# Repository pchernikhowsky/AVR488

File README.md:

# AVR488

A [Prologix](http://prologix.biz)<sup>TM</sup> compatible<sub><sup>(ish)</sup></sub> USB to [IEEE 488/GPIB/HP-IB](https://en.wikipedia.org/wiki/IEEE-488) controller interface based on the ATmega168/328 microcontroller.

## Description

I designed the AVR488 interface so that I could communicate with my various legacy Hewlett Packard / Agilent test instruments. There are numerous Arduino-based variations of USB/IEEE 488 interfaces out there already, but I prefer programming AVR devices down at the "bare metal" level using C code, so I came up with this version. Since it's necessary to construct a physical interface for the IEEE 488 connector anyway, it's easy enough to add an ATmega and driver ICs into that hardware design. Although it is intended to support a USB interface, a serial EIA-232 connection could also be implemented by deleting the USB interface IC and replacing it with an appropriate TTL to EIA-232 driver.

The embedded code size is approximately 13.5 KB and uses about 360 bytes of RAM, so there's more than enough free memory in an ATmega168 device. I have not included a bootloader (it avoids annoying startup delays and I prefer programming the ATmega directly using an ISP interface). If desired, there are many bootloaders available that could first be flashed to the device and then used to upload the AVR488 firmware.

**NOTE**: only controller mode (`++mode 1`) is implemented at this time, as I had no need for device mode. The latter is a possible future enhancement.

## Getting Started

### Dependencies

AVR488 supports both ATmega168 or ATmega328 devices (both the 10 and 20 MHz variants).

* Requires [MicroChip Studio 7 for AVR devices](https://www.microchip.com/en-us/tools-resources/develop/microchip-studio) for building the firmware.
* An ISP programmer (AVRISP MKII, AVR JTAG ICE, etc.) is needed to program the flash memory and set the fuses.

### Hardware Interfaces
* A USB 2.0 interface is provided by an [MCP2221A](https://www.microchip.com/en-us/product/MCP2221A) USB to TTL IC for connection to a host device (computer).
* The fully level-compliant IEEE 488 interface is implemented using the [SN75160](https://www.ti.com/lit/gpn/sn75als160) and [SN75161](https://www.ti.com/lit/gpn/sn75als161) driver ICs for connection to IEEE 488 devices.
* A direct serial EIA-232 interface could be implemented by using a [MAX232](https://www.ti.com/product/MAX232) (or equivalent) IC.

### Building and Installing the Firmware

1. Create a new project in MicroChip Studio and select the appropriate ATmega device.
2. Add the *.c and *.h files to the project.
3. Build the solution in MicroChip Studio.
4. Burn the code to your ATmega device.
5. Set the correct [fuses](Hardware/fuses.png):
   - Enable 8 MHz internal RC oscillator.
   - Disable divide by 8 clock divider (CKDIV8).
   - Enable brown-out detection (to provide protection against EEPROM corruption).
7. Connect the USB interface to a host computer and the IEEE 488 port to a device/instrument.
8. Upon first power-up, default settings will be stored in EEPROM. Settings can be changed and saved to EEPROM as required.
9. Enjoy!

When the AVR488 is first connected to a computer it will create a new USB serial port. The internal baud rate for the AVR488 serial port is fixed at 38400 bps (this can only be altered by changing a #define in the source code and reflashing). Thus, you MUST set the baud rate in your PC software (terminal program, etc.) to 38400 bps. A simple test to confirm that communications is fully working is to type the command "++help" (without the quotes). This should return a list available commands.

## Hardware Construction and Setup

You will need to construct your own hardware to support various ICs (ATmega168/328, MCP2221A, and SN75160/161) and the appropriate USB and IEEE 488 interface connectors. To make it easier, a full hardware design including [schematic](Hardware/AVR488-schematic.pdf), [bill of materials](Hardware/AVR488-BOM.csv), and PCB layout in KiCad format are provided. The PCB hardware and components have been selected to be hacker/hobbyist friendly; through-hole components are used exclusively. I ordered my PCBs from [JLCPCB](https://jlcpcb.com/), but feel free to use your preferred vendor. The PCB has been designed to fit inside a [Hammond 1593BB](https://www.hammfg.com/electronics/small-case/plastic/1593.pdf) plastic enclosure. A [dimensioned label](Hardware/AVR488-label.pdf) (including LED drilling dimensions) is also provided.

For simplicity, and to save pins, the internal 8 MHz RC oscillator in the ATmega168/328 is used as the clock source, so no external oscillator or crystal is required.

For diagnostic purposes, three LED outputs are provided:
* TE (Talk Enable): flashes when the TE signal to the IEEE 488 drivers goes high for driving data onto the bus.
* SRQ (Service Request): lights when the SRQ line is asserted, indicating that a device requires polling for status.
* STATUS: flashes during startup and then is continuously toggled when the watchdog timer is reset to indicate active processing (the toggling is around 130 kHz, so the LED is slightly dimmer than when fully on).

## Command List

The AVR488 command set is intended to be mostly compatible with the [Prologix GPIB-USB (HPIB-USB Controller)](http://prologix.biz/gpib-usb-controller.html). All commands are preceded by two plus signs (++). Any input not preceded by ++ is passed directly to the connected device(s). Input and commands from the host are buffered in a 254 byte buffer and then transmitted when either a CR (carriage return) or LF (line feed) character is received from the host. Not all Prologix commands have been implemented, and some do not operate exactly the same as the Prologix interface. Also, some extensions have been added for troubleshooting purposes (e.g., `debug` and `xdiag`) or for ease of use (e.g., `echo`).

Values enclosed in `[]` are optional. If a value is provided, the `[]` should not be included.

#### `++addr [n]`
Tell the interface which device to address (must be between 1 and 30). If no address is specified, the current device address will be displayed.

#### `++auto [n]`
Enable (1) or disable (0) automatic read-after-write when a "?" is included in the command sent to the device. If no value is provided, the current auto setting will be displayed.

#### `++clr`
Send a Select Device Clear (SDC) command to the currently addressed device.

#### `++debug [n]`
Enable simple (1), more verbose (2), or disable (0) debug logging messages. Convenient for troubleshooting problematic connections. If no value is provided, the current debug setting will be displayed.

#### `++default`
Emulates functionality of the AR488 command with the same name. The interface configuration is set with the following parameters:
* auto:	0
* eoi:	0 (disabled)
* eos:	0 (CR+LF)
* eot_enable:	0 (disabled)
* eot_char:	0
* address: 0
* read_tmo_ms:	1200
* echo: 0
* debug: 0

#### `++echo [n]`
Enable (1) or disable (0) echoing of characters received from USB port. Most IEEE 488 adapters require the sending application to enable local echo, but this is provided as an alternative. If no value is provided, the current echo setting will be displayed.

#### `++eoi [n]`
Enable (1) or disable (0) asserting the EOI line when the last byte is sent. If no value is provided, the current eoi setting will be displayed.

#### `++eos [n]`
Select the terminator characters to be appended to messages sent to the device: 0=CR+LF, 1=CR, 2=LF, 3=None. If no value is provided, the current eos setting will be displayed.

#### `++eot_char [n]`
ASCII code of character to be appended to messages received from the device (when EOI is used). If no value is provided, the current eot_char setting will be displayed.

#### `++eot_enable [n]`
Controls whether the eot_char is apprended to received messages. If no value is provided, the current eot_enable setting will be displayed.

#### `++help`
Print a list of commands and explanations.

#### `++ifc`
Issue an IEEE 488 interface clear by asserting the IFC line for 150 microseconds.

#### `++llo`
Disable front panel operation of the currently addressed device by sending the Local Lockout (LLO) command.

#### `++loc`
Enable front panel operation of the currently addressed device by sending the Go To Local (GTL) command.

#### `++mode [n]`
Compatibility-only command - we are always a controller. Any value provided is ignored and queries always return mode 1.

#### `++read`
Read from the currently addressed device until the eos terminating characters are received or a timeout occurs.

#### `++read eoi`
Read from the currently addressed device until either EOI is asserted, the eos terminating characters are received, or a timeout occurs.

#### `++read_tmo_ms [n]`
Sets the timeout value, in milliseconds, for the read and spoll commands. The default timeout is 1000 ms. If no value is provided, the current read_tmo_ms setting will be displayed.

#### `++rst`
Performs a power-on reset of the controller interface by forcing a watchdog timer timeout. Takes approximately 2 seconds.

#### `++savecfg 1`
Saves the current settings to EEPROM. Settings saved include: addr, eot_char, eot_enable, eos, eoi, auto, debug, and echo. Settings are **not** saved automatically when they are changed (to prevent unnecessary wear on the EEPROM). The value "1" must be included or the command is ignored.

#### `++spoll [n]`
Read the device status byte by issuing a Serial Poll command. If no address is specified the serial poll request will be sent to the currently addressed device.

#### `++srq`
Query the status of SRQ line. Returns 0 if the line is not asserted and 1 if asserted.

#### `++trg [n]`
Issue a Group Execute Trigger (GET) to a device. If no address is specified the trigger will be sent to the currently addressed device.

#### `++ver`
Query the current AVR488 firmware version.

#### `++xdiag`
Show the current state of the ATmega IO pins (for troubleshooting purposes).

## Version History

* 1.1
    * Firmware changes to improve AR488 and Prologix compatibility.
* 1.0
    * Initial Release

## License

This project is licensed under the GPL-3.0 License. See the [LICENSE](LICENSE) file for details.

## Acknowledgments

Inspiration, code snippets, libraries.
* [AR488](https://github.com/Twilight-Logic/AR488)
* [atmega-gpib](https://github.com/pepaslabs/atmega-gpib)
* [gpibusb-firmware](https://github.com/Galvant/gpibusb-firmware)
* [Peter Fleury's interrupt-driven UART library](http://www.peterfleury.epizy.com/doxygen/avr-gcc-libraries/group__pfleury__uart.html)

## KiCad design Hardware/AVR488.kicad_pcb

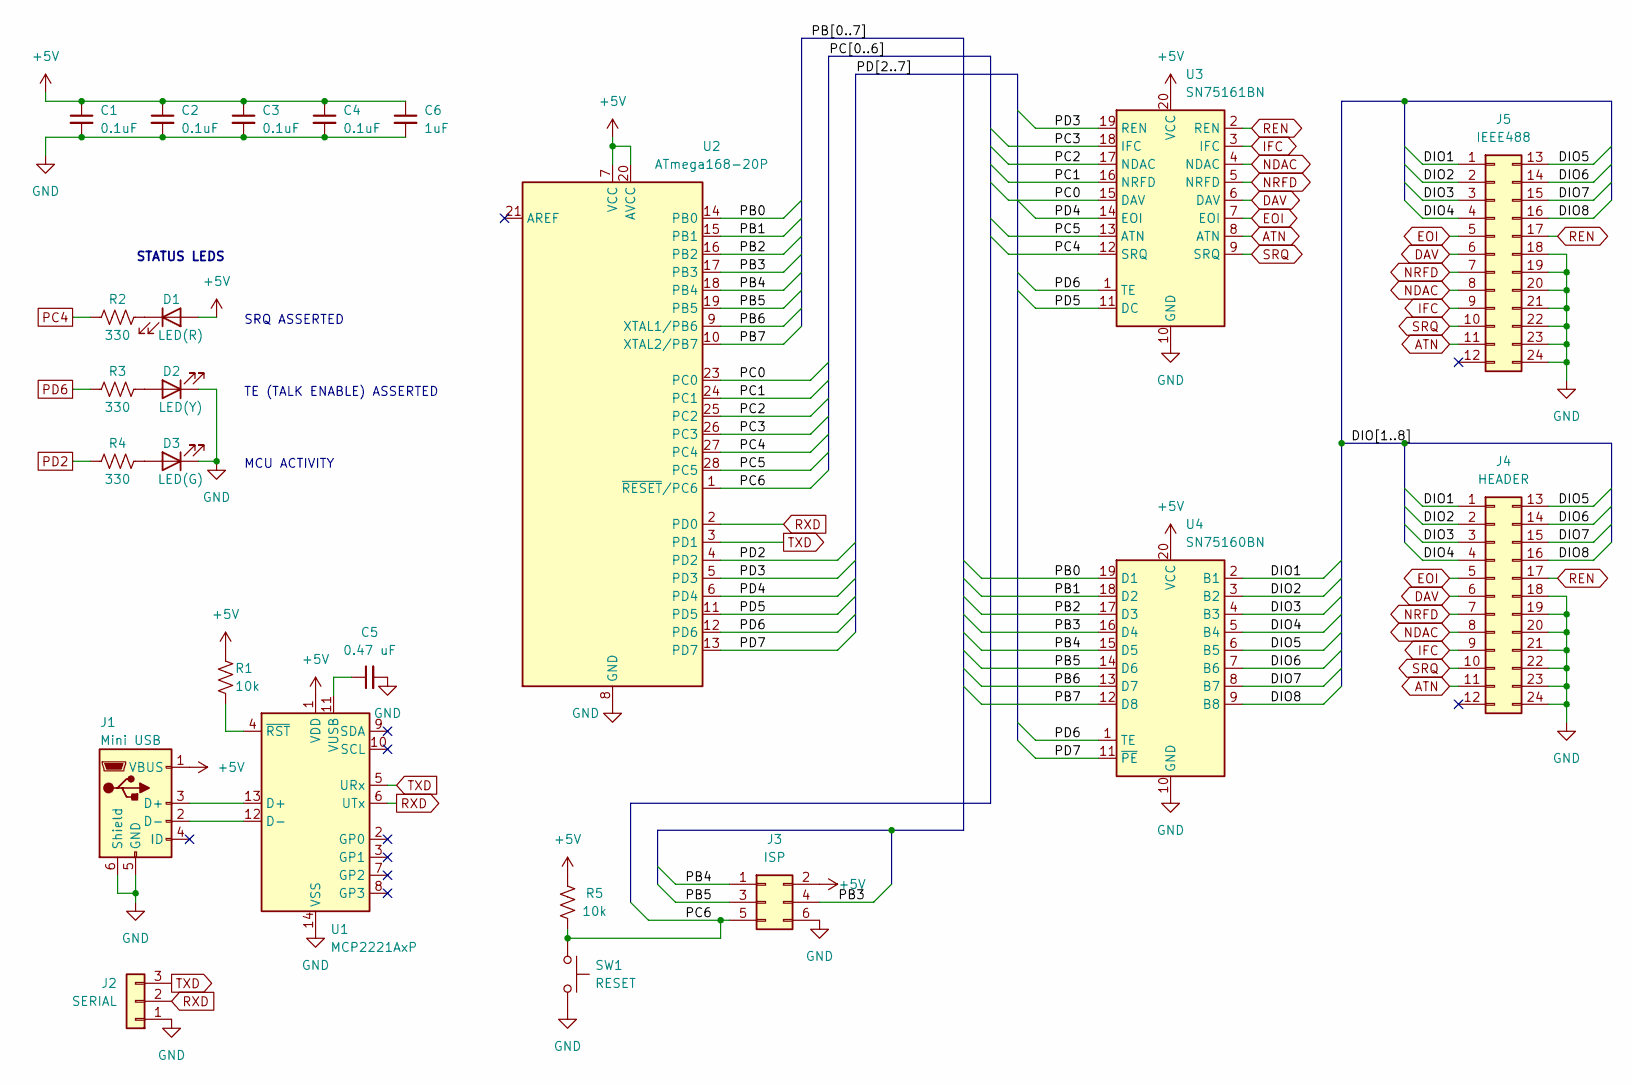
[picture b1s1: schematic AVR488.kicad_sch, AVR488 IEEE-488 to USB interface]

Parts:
C1, C2, C3, C4: 0.1uF; C_Disc_D3.0mm_W1.6mm_P2.50mm; PartNo C320C104K5R5TA
C5: 0.47 uF; C_Rect_L7.0mm_W2.5mm_P5.00mm; PartNo C330C474M5R5TA
C6: 1uF; CP_Radial_D5.0mm_P2.50mm; PartNo UVK1H010MDD1TD
D1: LED(R); LED_D5.0mm; PartNo LTL-307E
D2: LED(Y); LED_D5.0mm; PartNo LTL-307Y
D3: LED(G); LED_D5.0mm; PartNo LTL-307G
J1: Mini USB; 2172034-1; PartNo 2172034-1
J2: SERIAL; PinHeader_1x03_P2.54mm_Vertical
J3: ISP; PinHeader_2x03_P2.54mm_Vertical
J4: HEADER; PinHeader_2x12_P2.54mm_Vertical
J5: IEEE488; 112-024-113R001; PartNo 112-024-113R001
R1, R5: 10k; R_Axial_DIN0207_L6.3mm_D2.5mm_P10.16mm_Horizontal; PartNo CF18JT10K0
R2, R3, R4: 330; R_Axial_DIN0207_L6.3mm_D2.5mm_P10.16mm_Horizontal; PartNo CF18JT330R
SW1: RESET; B3F-6002; PartNo B3F-6002
U1: MCP2221AxP; DIP-14_W7.62mm; PartNo MCP2221A-I/P
U2: ATmega168-20P; DIP-28_W7.62mm; PartNo ATMEGA168A-PU
U3: SN75161BN; DIP-20_W7.62mm; PartNo SN75161BN
U4: SN75160BN; DIP-20_W7.62mm; PartNo SN75160BN

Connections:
+5V: C1.1, C2.1, C3.1, C4.1, C6.1, D1.2 (A), J1.1 (VBUS), J3.2, R1.1, R5.2, U1.1 (VDD), U2.7 (VCC), U2.20 (AVCC), U3.20 (VCC), U4.20 (VCC)
/DIO1: J4.1, J5.1, U4.2 (B1)
/DIO2: J4.2, J5.2, U4.3 (B2)
/DIO3: J4.3, J5.3, U4.4 (B3)
/DIO4: J4.4, J5.4, U4.5 (B4)
/DIO5: J4.13, J5.13, U4.6 (B5)
/DIO6: J4.14, J5.14, U4.7 (B6)
/DIO7: J4.15, J5.15, U4.8 (B7)
/DIO8: J4.16, J5.16, U4.9 (B8)
/PB0: U2.14 (PB0), U4.19 (D1)
/PB1: U2.15 (PB1), U4.18 (D2)
/PB2: U2.16 (PB2), U4.17 (D3)
/PB3: J3.4, U2.17 (PB3), U4.16 (D4)
/PB4: J3.1, U2.18 (PB4), U4.15 (D5)
/PB5: J3.3, U2.19 (PB5), U4.14 (D6)
/PB6: U2.9 (XTAL1/PB6), U4.13 (D7)
/PB7: U2.10 (XTAL2/PB7), U4.12 (D8)
/PC0: U2.23 (PC0), U3.15 (DAV)
/PC1: U2.24 (PC1), U3.16 (NRFD)
/PC2: U2.25 (PC2), U3.17 (NDAC)
/PC3: U2.26 (PC3), U3.18 (IFC)
/PC5: U2.28 (PC5), U3.13 (ATN)
/PC6: J3.5, R5.1, SW1.1, U2.1 (~RESET/PC6)
/PD3: U2.5 (PD3), U3.19 (REN)
/PD4: U2.6 (PD4), U3.14 (EOI)
/PD5: U2.11 (PD5), U3.11 (DC)
/PD7: U2.13 (PD7), U4.11 (~PE)
ATN: J4.11, J5.11, U3.8 (ATN)
DAV: J4.6, J5.6, U3.6 (DAV)
EOI: J4.5, J5.5, U3.7 (EOI)
GND: C1.2, C2.2, C3.2, C4.2, C5.2, C6.2, D2.1 (K), D3.1 (K), J1.5 (GND), J1.6 (Shield), J2.1, J3.6, J4.18, J4.19, J4.20, J4.21, J4.22, J4.23, J4.24, J5.18, J5.19, J5.20, J5.21, J5.22, J5.23, J5.24, SW1.2, U1.14 (VSS), U2.8 (GND), U2.22 (GND), U3.10 (GND), U4.10 (GND)
IFC: J4.9, J5.9, U3.3 (IFC)
NDAC: J4.8, J5.8, U3.4 (NDAC)
NRFD: J4.7, J5.7, U3.5 (NRFD)
unnamed: C5.1, U1.11 (VUSB)
unnamed: D1.1 (K), R2.2
unnamed: D2.2 (A), R3.2
unnamed: D3.2 (A), R4.2
unnamed: J1.2 (D-), U1.12 (D-)
unnamed: J1.3 (D+), U1.13 (D+)
unnamed: R1.2, U1.4 (~RST)
PC4: R2.1, U2.27 (PC4), U3.12 (SRQ)
PD2: R4.1, U2.4 (PD2)
PD6: R3.1, U2.12 (PD6), U3.1 (TE), U4.1 (TE)
REN: J4.17, J5.17, U3.2 (REN)
RXD: J2.2, U1.6 (UTx), U2.2 (PD0)
SRQ: J4.10, J5.10, U3.9 (SRQ)
TXD: J2.3, U1.5 (URx), U2.3 (PD1)

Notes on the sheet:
SRQ ASSERTED
STATUS LEDS
TE (TALK ENABLE) ASSERTED
MCU ACTIVITY

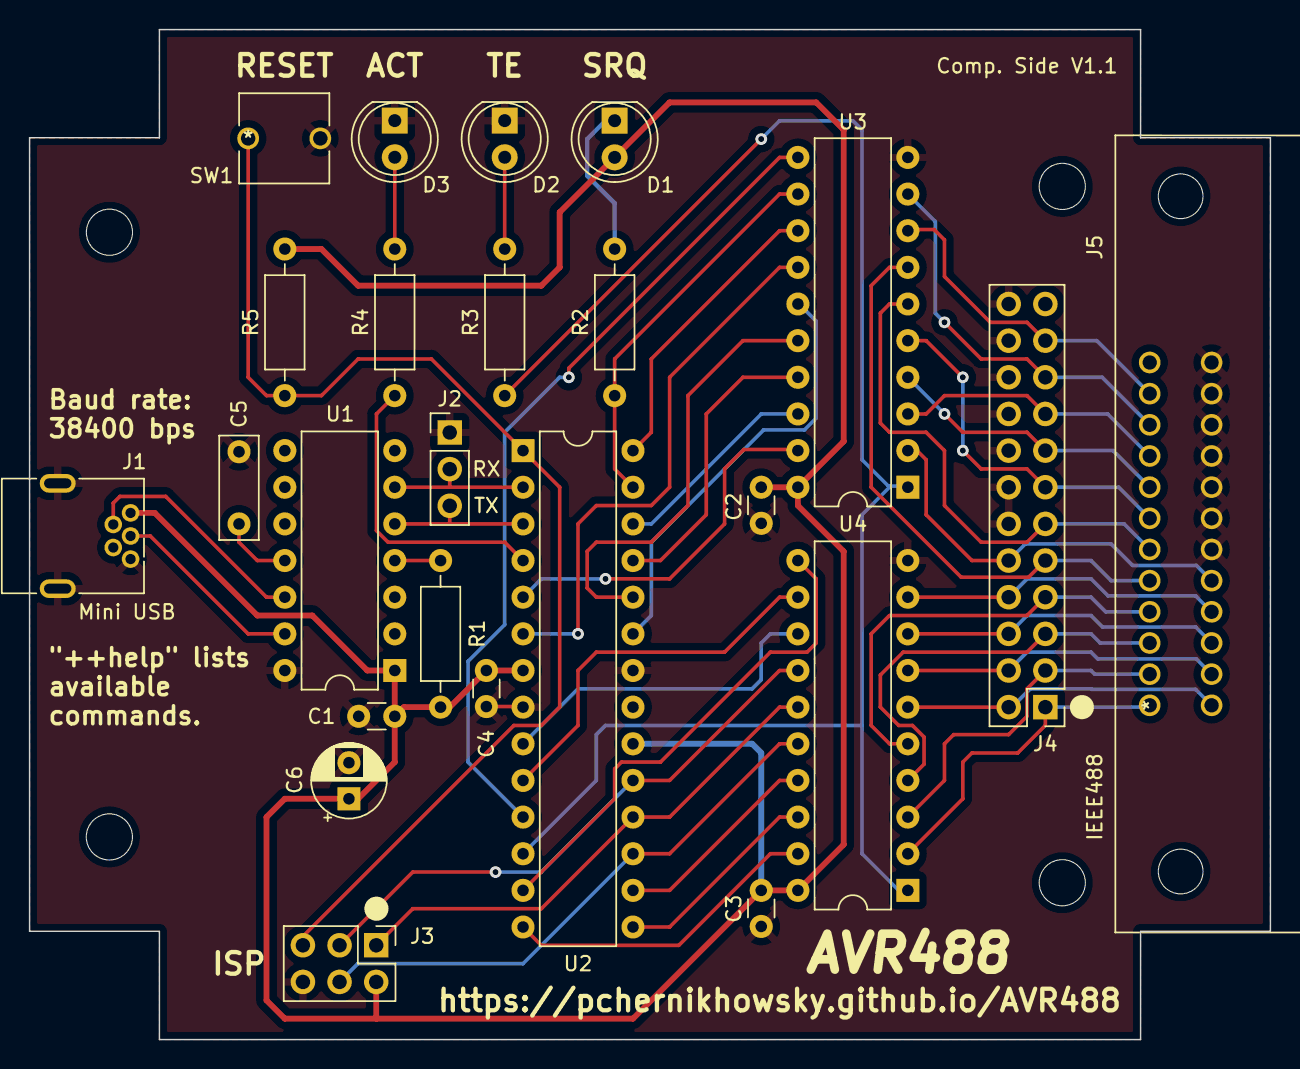
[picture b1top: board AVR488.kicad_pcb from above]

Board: 2 copper layers, 86.0 x 70.0 mm, 28 parts (0 on the bottom side), 48 nets.

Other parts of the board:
REF1, REF2, REF3, REF4: MountingHole_3.2mm_M3

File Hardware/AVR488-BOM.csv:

Qty,Reference(s),Value,Manufacturer,Digi-Key Part Number,PartNo
4,"C1, C2, C3, C4",0.1uF,KEMET,399-4264-ND,C320C104K5R5TA
1,C5,0.47 uF,KEMET,399-14020-ND,C330C474M5R5TA
1,C6,1uF,Nichicon,493-12567-1-ND,UVK1H010MDD1TD
1,D1,LED(R),Lite-On,160-1705-ND,LTL-307E
1,D2,LED(Y),Lite-On,160-1703-ND,LTL-307Y
1,D3,LED(G),Lite-On,160-1706-ND,LTL-307G
1,J1,Mini USB,TE Connectivity AMP Connectors,A135698-ND,2172034-1
1,J2,SERIAL,Amphenol ICC (FCI),10129378-903001BLF-ND,10129378-903001BLF
1,J3,ISP,Amphenol ICC (FCI),10129381-906001BLF-ND,10129381-906001BLF
1,J4,HEADER,Amphenol ICC (FCI),10129381-924001BLF-ND,10129381-924001BLF
1,J5,IEEE488,NorComp Inc.,1024RMA-ND,112-024-113R001
2,"R1, R5",10k,Stackpole Electronics Inc,CF18JT10K0TR-ND,CF18JT10K0
3,"R2, R3, R4",330R,Stackpole Electronics Inc,CF18JT330RTR-ND,CF18JT330R
1,SW1,RESET,Omron,SW797CT-ND,B3F-6002
1,U1,MCP2221AxP,Microchip Technology,MCP2221A-I/P-ND,MCP2221A-I/P
1,U2,ATmega168-20P,Microchip Technology,ATMEGA168V-10PU-ND,ATMEGA168V-10PU
1,U3,SN75161BN,Texas Instruments,296-6847-5-ND,SN75161BN
1,U4,SN75160BN,Texas Instruments,296-6845-5-ND,SN75160BN
3,,LED Standoffs,Bivar Inc.,ELM3-440-ND,ELM 3-440
2,,#4-40 connector mounting screws,Keystone,36-9900-ND,9900
1,,Enclosure,Hammond Manufacturing,HM1376-ND,1593BBGY

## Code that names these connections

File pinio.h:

/*
 * pinio.h
 *
 * Created: 30-Dec-2021 3:54:58 PM
 *  
 */


#ifndef PINIO_H_
#define PINIO_H_

// ATmega168/328 -> GPIB pin mapping (using the MCP2221A)
//
//                       +-----------\_/-----------+
//        /RESET        -|1  PC6             PC5 28|-        GPIB 11: ATN
// MCP2221 6: TX        -|2  PD0             PC4 27|-        GPIB 10: SRQ
// MCP2221 5: RX        -|3  PD1             PC3 26|-        GPIB  9: IFC
//    STATUS LED        -|4  PD2             PC2 25|-        GPIB  8: NDAC
//  GPIB 17: REN        -|5  PD3             PC1 24|-        GPIB  7: NRFD
//   GPIB 5: EOI        -|6  PD4             PC0 23|-        GPIB  6: DAV
//                  Vcc -|7                      22|- GND
//                  GND -|8                      21|- AREF
//  GPIB 15: DIO7       -|9  PB6                 20|- AVcc
//  GPIB 16: DIO8       -|10 PB7             PB5 19|-        GPIB 14: DIO6
//     SN75161 DC       -|11 PD5             PB4 18|-        GPIB 13: DIO5
// SN75160/161 TE       -|12 PD6             PB3 17|-        GPIB  4: DIO4
//     SN75160 PE       -|13 PD7             PB2 16|-        GPIB  3: DIO3
//   GPIB 1: DIO1       -|14 PB0             PB1 15|-        GPIB  2: DIO2
//                       +-------------------------+

// AVR port to GPIB pin definitions
#define DAV  PINC0
#define NRFD PINC1
#define NDAC PINC2
#define IFC  PINC3
#define SRQ  PINC4
#define ATN  PINC5

// Use the high bit to indicate PORTD pins
#define REN (PIND3 | 0x80)
#define EOI (PIND4 | 0x80)
#define DC  (PIND5 | 0x80)
#define TE  (PIND6 | 0x80)
#define PE  (PIND7 | 0x80)
#define LED_STATUS (PIND2 | 0x80) // continuously toggled by _wdt_reset() to indicate life

// Defines for pin control using GPIB negative logic
#define ASSERT output_low
#define DEASSERT output_high
#define FLOAT output_float

// Prototypes for pin control functions
extern void output_float(uint8_t bit);
extern void output_high(uint8_t bit);
extern void output_low(uint8_t bit);
extern void toggle_output(uint8_t bit);
extern uint8_t input(uint8_t bit);

#endif /* PINIO_H_ */

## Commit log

2022-02-06 First release
2022-02-06 Included schematics
2022-02-06 Uploaded image
2022-02-06 Added prototype image
2022-02-07 Renamed folder.
2022-02-15 Revised version handling for bettter Prologix compatibility
2022-02-20 Fixed null command handling.
2022-02-27 Set theme jekyll-theme-slate
2022-03-26 Added KiCad hardware files.
2022-03-26 Update README.md
    Updated with KiCad hardware info.
2022-03-26 Renamed file
2022-03-26 Added hardware image
2022-03-26 Update README.md
    Added hardware image.
2022-03-26 Added bill of materials
2022-04-25 Bug fixes. Also improved Prologix and AR488 command set compatibility.
2022-05-10 Added enclosure label.
2022-05-30 Added .hex file
2022-06-03 Rename AVR488.hex to AVR488-M328P.hex
    Renamed - for ATmega328P mcu.
